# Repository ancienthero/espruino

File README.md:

# espruino
__espruino__ is a Javascript interpreter for STM32 ARM microcontrollers.
This repo contains my modules, projects, tutorials.

:tada: :soon:

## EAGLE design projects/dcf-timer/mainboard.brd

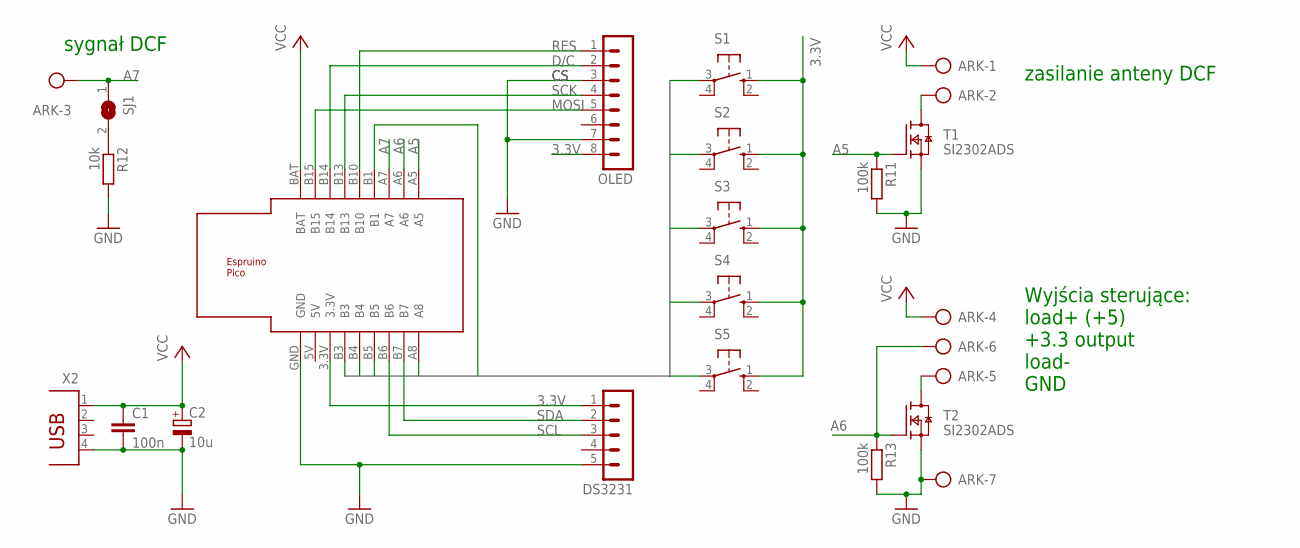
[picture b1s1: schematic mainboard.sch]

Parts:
ARK: AK500/7
C1: 100n; C1206K
C2: 10u; A/3216-18W
DS3231: MA05-1
OLED: MA08-1
R11, R13: 100k; M0805
R12: 10k; M0805
S1, S2, S3, S4, S5: 10-XX; B3F-10XX
SJ1: SJ
T1, T2: SI2302ADS; SOT23
U$1: ESPRUINO_PICO_0.1
X2: PN61729

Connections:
3.3V: DS3231.1, OLED.8, S1.1 (S), S2.1 (S), S3.1 (S), S4.1 (S), S5.1 (S), U$1.3.3V
A5: R11.1, T1.1 (G), U$1.A5
A6: ARK.6, R13.1, T2.1 (G), U$1.A6
A7: ARK.3, SJ1.1, U$1.A7
CS: ARK.7, C1.2, C2.-, DS3231.5, OLED.3, OLED.7, R11.2, R12.2, R13.2, T1.2 (S), T2.2 (S), U$1.GND, X2.4
D/C: OLED.2, U$1.B14
MOSI: OLED.5, U$1.B15
unnamed: R12.1, SJ1.2
unnamed: ARK.2, T1.3 (D)
unnamed: ARK.5, T2.3 (D)
RES: OLED.1, U$1.B10
S1: S1.3, U$1.B3
S2: S2.3, U$1.B4
S3: S5.3, U$1.B5
S4: S4.3, U$1.A8
S5: S3.3, U$1.B1
SCK: OLED.4, U$1.B13
SCL: DS3231.3, U$1.B6
SDA: DS3231.2, U$1.B7
VCC: ARK.1, ARK.4, C1.1, C2.+, U$1.BAT, X2.1

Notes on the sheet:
sygnał DCF
zasilanie anteny DCF
Wyjścia sterujące: load+ (+5) +3.3 output load- GND

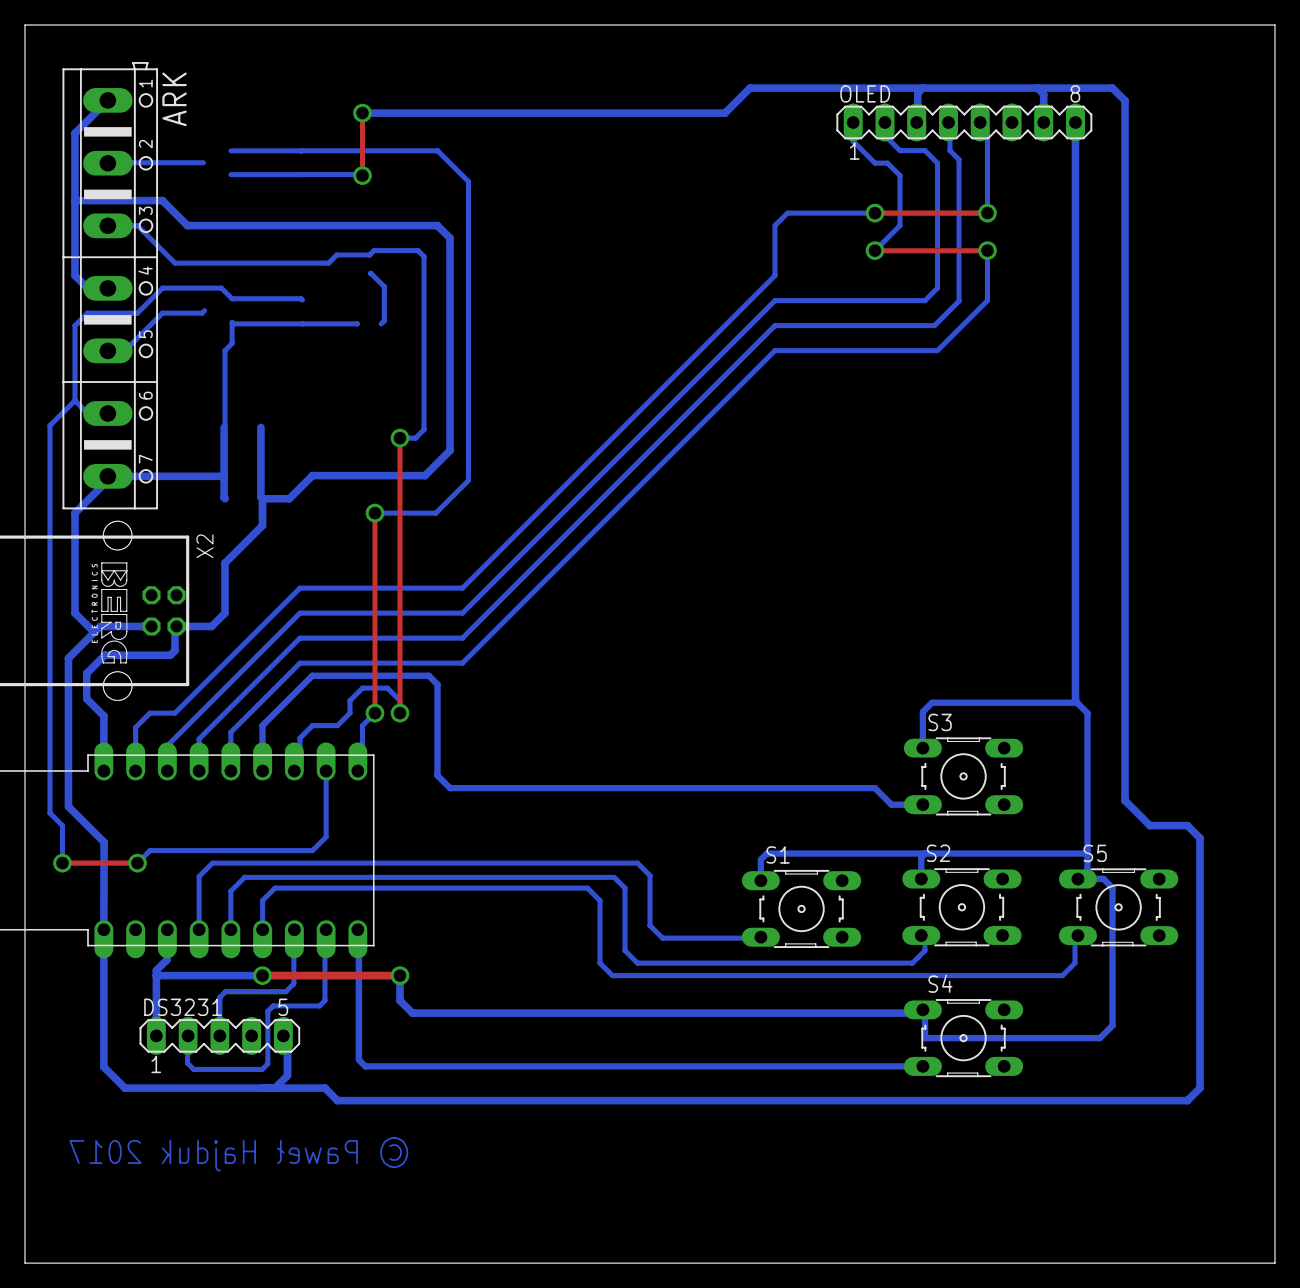
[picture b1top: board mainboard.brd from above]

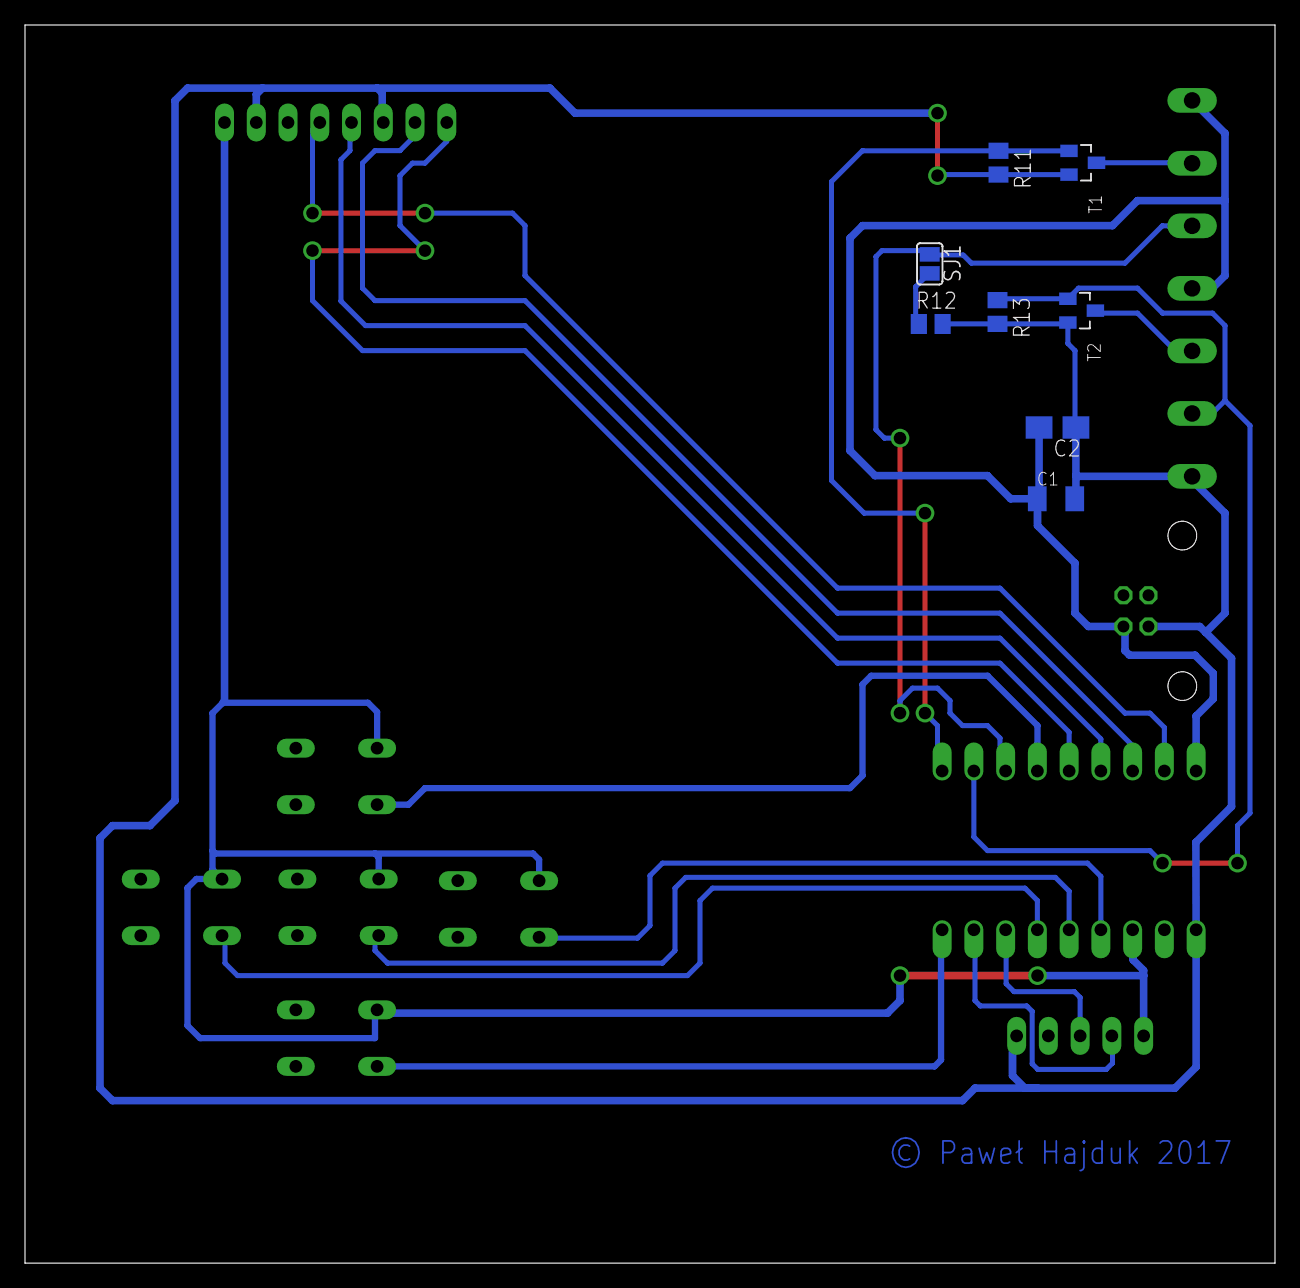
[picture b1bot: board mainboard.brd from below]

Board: 2 copper layers, 100.0 x 99.0 mm, 18 parts (8 on the bottom side), 20 nets.

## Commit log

2017-06-05 DS3231 module
2017-06-06 days as numbers 1-Sunday 2-Monday etc, same as js date object
2017-06-06 js date object variable ranges
2017-06-07 default DST option off
2017-07-11 removed summer time support, it shouldn't be handled in this module
2017-07-11 README update
2017-09-01 dcf timer initial commit
2017-10-10 Added timeSwitchViews.xml
2017-10-10 Added timeSwitchViews.png
2017-10-10 unnecessary comment
2017-10-11 documentation for ds3231 module
2017-10-11 resize image
2017-10-11 Removed unnecessary comment
2017-10-14 minified version of DS3231.js
2017-10-19 eagle schematic and board
2017-10-19 typo
2017-11-28 extended on/off times limit, changes to lookUpTimes view
2017-12-20 pdf files, removed older version
2017-12-21 add gitignore

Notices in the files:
projects/dcf-timer/mainboard.brd:
© Paweł Hajduk 2017
parts and their libraries:
NXP_60_26022015: This library may be distributed and adapted freely for any purpose, as long as NXP is credited and any new creation is licensed under the same terms.
